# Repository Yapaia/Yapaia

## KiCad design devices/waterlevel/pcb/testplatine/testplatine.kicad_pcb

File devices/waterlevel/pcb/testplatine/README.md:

# Testplatine v2 – Bahnbreiten ausmessen

Kleine Platine (100 × 100 mm, 2 Lagen, 1,6 mm FR4), um vor der 50-cm-Sonde
zu messen, welche Bahnbreite und welche Isolierung am ESP32-S3 am besten
funktionieren. Sechs Finger mit je einer Messbahn, dazu ein Leerkanal. Der
ESP (**Seeed XIAO ESP32S3**) sitzt direkt auf der Platine, alle Kanäle werden
gleichzeitig gemessen.

| Vorderseite | Rückseite |
|---|---|
|  |  |

## Warum der XIAO ESP32S3

- Belegung ist eindeutig dokumentiert (keine wechselnden Klone wie beim
  „S3 SuperMini“): D0–D5 = GPIO1–6, D8–D10 = GPIO7–9 – das sind alles
  Touch-Eingänge (T1–T9 laut `arduino-esp32/variants/XIAO_ESP32S3/pins_arduino.h`).
- Klein (21 × 17,8 mm), zwei Reihen à 7 Pins im 2,54-mm-Raster, Reihenabstand
  15,24 mm (aus Seeeds KiCad-Bibliothek).
- USB-C, 3,3-V-Regler, in ESPHome als `seeed_xiao_esp32s3`.
- Antenne extern (U.FL) – die mitgelieferte Antenne anstecken.

## Aufbau

- **Kopf** (oben, 39,5 mm, bleibt trocken): XIAO ESP32S3 (U1, Bauteilseite
  oben, USB-C zeigt nach links über die Platinenkante), Serienwiderstände
  R1–R7 (510 Ω, **bedrahtet**, stehend im 2,54-mm-Raster, versetzt in zwei
  Reihen) direkt an den Pins, zwei M3-Löcher zum Aufhängen.
  Rückseite: GND als Gitter (wie von Espressif empfohlen).
- **Finger** (60 mm lang, 14 mm breit): mittig die Messbahn, links und rechts
  GND-Streifen (Vorder- und Rückseite, 1,5 mm Abstand zur Messbahn). Unter der
  Messbahn ist kein Kupfer. Alles unter Lötstopplack, im nassen Bereich keine
  Durchkontaktierungen, Kupfer endet 3 mm vor der Unterkante.
- **Skala** auf der Rückseite: Striche alle 1 cm, 0 = unteres Ende der Messbahn
  (Messbahn reicht bis 5,5 cm).

| Kanal | XIAO-Pin | GPIO | Bahnbreite | Isolierung | erwartet bei 5,5 cm (Lack 10 / 20 / 30 µm) |
|---|---|---|---|---|---|
| S1 | D0 | 1 | 0,15 mm | Lack | 28 / 14 / 9 pF |
| S2 | D1 | 2 | 0,2 mm | Lack | 37 / 18 / 12 pF |
| S3 | D2 | 3 | 0,3 mm | Lack | 55 / 27 / 18 pF |
| S4 | D3 | 4 | 0,5 mm | Lack | 90 / 45 / 30 pF |
| S5 | D4 | 5 | 1,0 mm | Lack, danach Schrumpfschlauch | 174 / 87 / 58 pF (mit Schlauch ≈ 3,5 pF) |
| S6 | D5 | 6 | 3,0 mm | Lack, danach Schrumpfschlauch | 459 / 230 / 153 pF (mit Schlauch ≈ 9 pF) |
| S7 | D8 | 7 | – (endet im Kopf) | – | nur Grundkapazität, Bezug für Drift |
| GND | GND | | | | |

Frei bleiben D6/D7 (UART) und D9/D10 (GPIO8/9, auch Touch – Reserve).
Werte aus `../../rechner.py`. Bei S6 sind die GND-Streifen nur 4,5× so breit
wie die Messbahn; das kostet dort ca. 18 % Signal (ist eingerechnet).

## Bestellen

Fertigungsdaten: [`fertigung/testplatine-gerber.zip`](fertigung/testplatine-gerber.zip)
(Gerber + Bohrdaten, ohne X2-Erweiterungen, wie JLCPCB es empfiehlt). Die ZIP
**unverändert** hochladen – nicht entpacken. Mit einem unabhängigen Gerber-Viewer
(gerbv) geprüft: Umriss, Schlitze, Bohrungen und Lagen stimmen.

Einstellungen bei JLCPCB (sonst Standard lassen):

| Option | Wert |
|---|---|
| Base Material | FR-4 |
| Layers | 2 |
| Dimension | 100 × 100 mm (wird erkannt) |
| PCB Qty | 5 (Minimum) |
| PCB Thickness | 1.6 mm |
| PCB Color | Green (für den Vergleich mit der späteren Sonde dieselbe Farbe nehmen – andere Farben haben andere Lackdicken) |
| Silkscreen | White |
| Surface Finish | HASL (lead free) |
| Outer Copper Weight | 1 oz |
| Via Covering | Tented |
| Mark on PCB / Remove Order Number | egal; die Nummer stört nicht |
| PCB Assembly | **nein** (wir löten selbst) |

Die Schlitze zwischen den Fingern sind im Umriss enthalten, dafür ist keine
Zusatzoption nötig. Kleinste Werte: Bahn 0,15 mm, Abstand 0,3 mm, Bohrung
0,3 mm – alles im Standard von JLCPCB.

Neu erzeugen (KiCad 7): `./fertigung.sh` – baut `testplatine.kicad_pcb` aus
`erzeuge.py` und exportiert Gerber, Bohrdaten und Vorschau. Die Maße stehen
oben in `erzeuge.py` und lassen sich dort ändern. Der DRC meldet nur die
offenen Enden der Messbahnen (gewollt: Elektroden).

## Bestücken und Anschließen

1. R1–R7: 510 Ω, bedrahtet (z. B. Metallschicht 0,25 W, Bauform 0207).
   **Stehend** einbauen: Körper auf das Pad mit dem Kreis im Bestückungsdruck,
   den anderen Draht oben umbiegen und ins Nachbarloch. Keine SMD-Teile.
2. XIAO ESP32S3 mit zwei 7-poligen Stiftleisten einlöten (oder Buchsenleisten,
   dann ist er wiederverwendbar). Bauteilseite nach oben, USB-C nach links –
   Pin D0 ist das eckige Pad, so steht es auch im Bestückungsdruck.
3. Antenne anstecken, Strom über USB-C.
4. ESPHome: [`testplatine.yaml`](testplatine.yaml) – meldet die Rohwerte aller
   sieben Kanäle an Home Assistant und loggt sie (`setup_mode`).
   Braucht `waterlevel_*`-Einträge in der `secrets.yaml`.

## Messablauf

1. **Trocken**: Rohwerte S1–S7 notieren (Grundwert).
2. In ein Gefäß mit **Leitungswasser** (z. B. hoher Messbecher, ≥ 11 cm breit)
   bis höchstens zur 5-cm-Marke (Kopf bleibt trocken!) in Schritten von 1 cm eintauchen, je 30 s warten, Rohwerte notieren
   (in HA als Verlauf). Erwartung: linear mit der Tiefe.
3. Rauschen bei fester Tiefe über 1 min ansehen (Signal/Rauschen > 5:1 je cm?).
4. Herausziehen: wie schnell geht der Wert auf den Grundwert zurück (Wasserfilm)?
5. **Drift**: 24 h in 4 cm Tiefe stehen lassen, S7 als Vergleich.
6. **Variante B**: S5/S6 mit Schrumpfschlauch (Kleber-frei, ohne
   Lufteinschlüsse) überziehen und Schritte 1–4 wiederholen.
7. Optional: Wasser mit etwas Salz / destilliertes Wasser – Einfluss der
   Leitfähigkeit.

Auswerten: Rohwert je cm und Rauschen je Kanal → Bahnbreite für die Sonde
festlegen, `rechner.py` mit der gemessenen Kapazität je mm abgleichen.

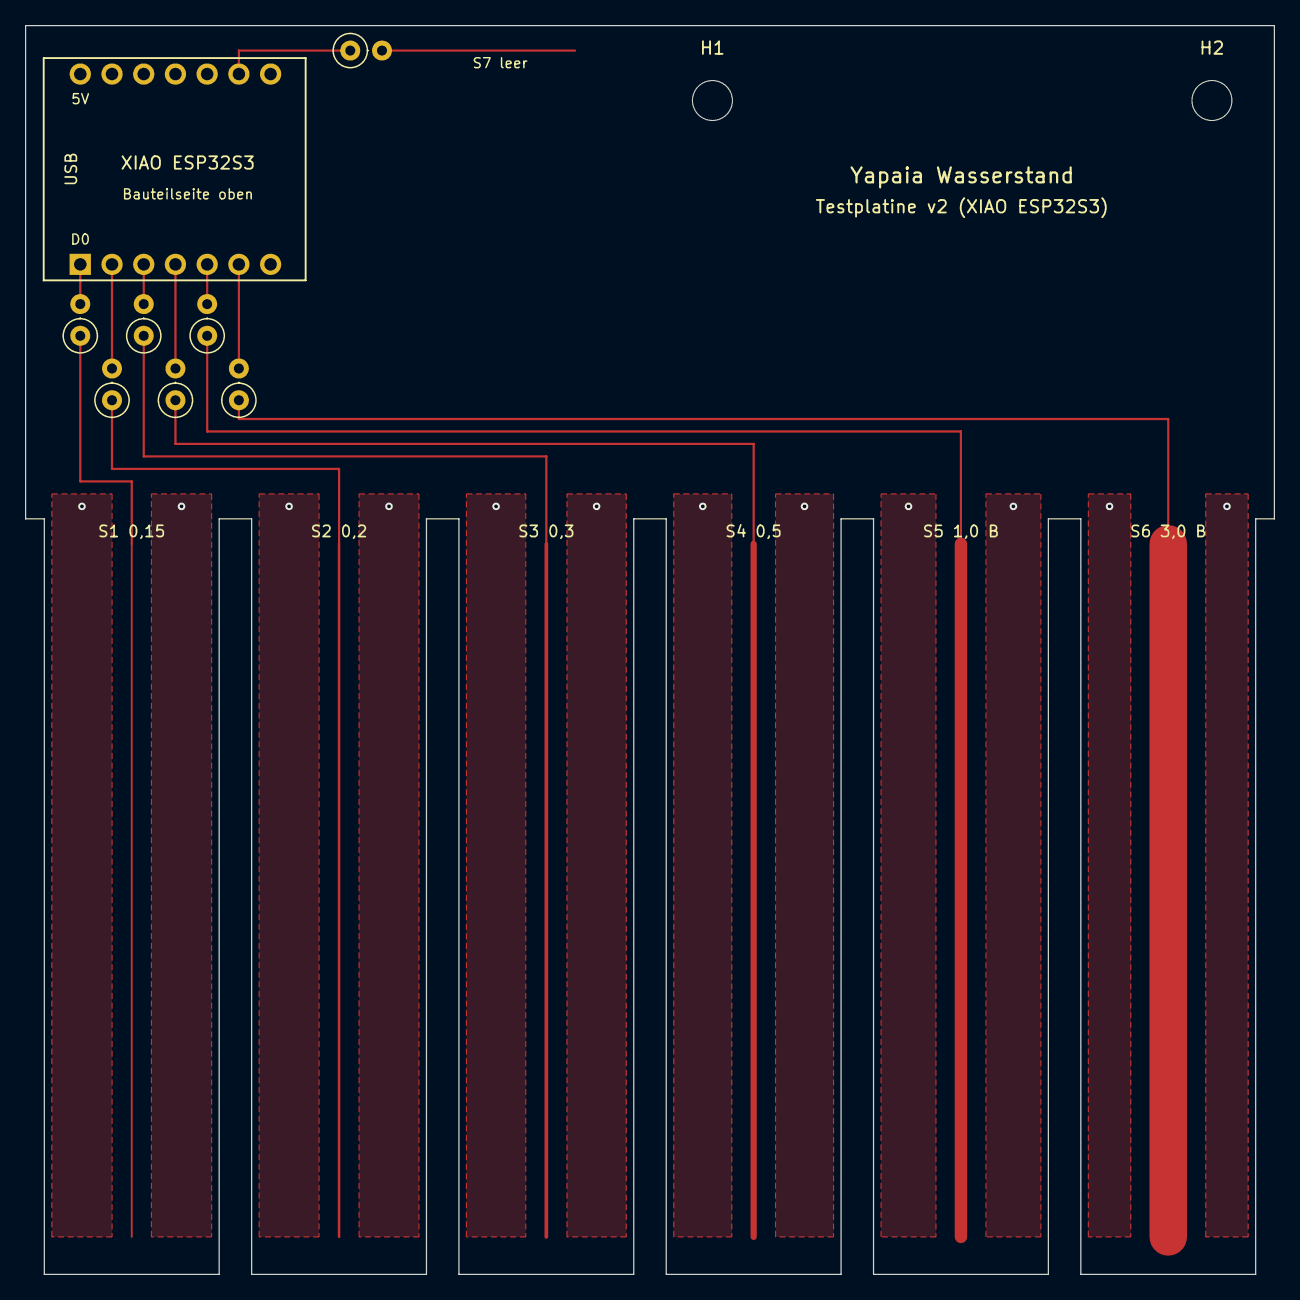
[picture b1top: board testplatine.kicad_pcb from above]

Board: 2 copper layers, 100.0 x 100.0 mm, 10 parts (0 on the bottom side), 7 nets.

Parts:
H1, H2: MountingHole_3.2mm_M3
R1, R2, R3, R4, R5, R6, R7: 510; R_Axial_DIN0207_L6.3mm_D2.5mm_P2.54mm_Vertical
U1: XIAO ESP32S3

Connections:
S1_PIN: R1.2, U1.1
S2_PIN: R2.2, U1.2
S3_PIN: R3.2, U1.3
S4_PIN: R4.2, U1.4
S5_PIN: R5.2, U1.5
S6_PIN: R6.2, U1.6
S7_PIN: R7.1, U1.9
